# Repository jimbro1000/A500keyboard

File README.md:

# A500 Keyboard HID Adapter
This is a (prototype) project to develop a simple adapter for the Amiga 500 
keyboard for connection via USB. The project is not particularly revolutionary,
other similar projects exist but require the use of more expensive 
microcontrollers while this solution aims to use the remarkably cheap RP2040
controller (aka Raspberry Pico)

## Components Used
Right now this is being built on a breadboard but the design is mirrored as
a KiCad project.

The initial approach is to utilise a pair of CD4050 hex non-inverting buffers
to manage level shifting between the keyboard (which operates at 5v) and the
RP2040 (operating at 3.3v).

The shift up to 5v is only required to drive LEDs on the keyboard so not actually
mandatory but in order to achieve full brightness the 5v is needed. This could
be achieved with a couple of transistors but the CD4050 chips are cheap enough
and readily available such that it is an equally simply solution.

If you don't care about the brightness of the LEDs then you could simply miss
the second CD4050 out and just jumper between two pairs of pins.

The inclusion of smoothing caps on the board is equally speculative. For the LED
drivers it should be completely unnecessary given the frequencies used. For the
keyboard data lines though it is strongly recommended to make sure the quality 
of transmission is maintained.

All in a single prepared board should cost roughly £14 (being somewhat pessimistic
with component prices). Given the price point on the PCB in batches of 10 and
similar bulk prices on the Pico board that could easily be reduced down to just 
£9 (being optimistic). Deleting the second CD4050 should save another £0.20-0.60
(if you're paying more that for CD4050s something is wrong).

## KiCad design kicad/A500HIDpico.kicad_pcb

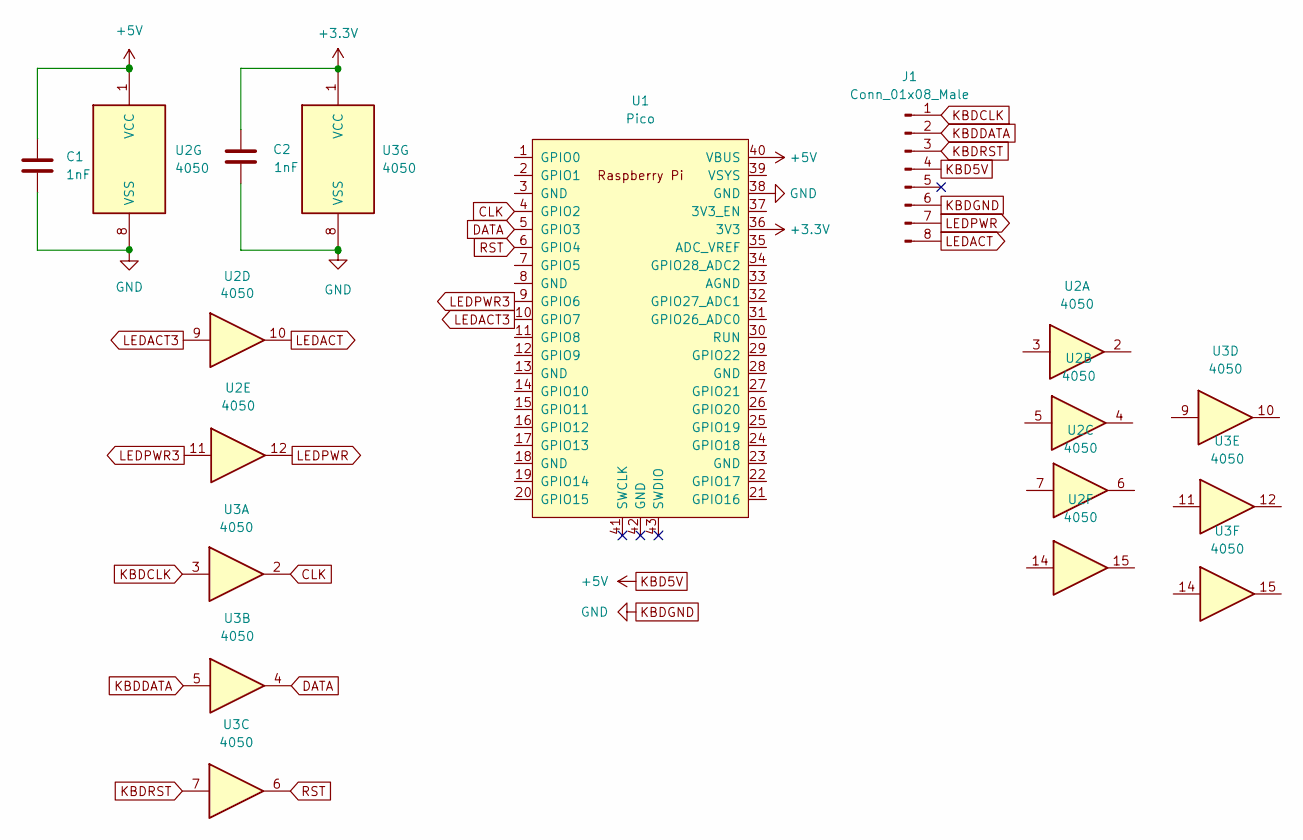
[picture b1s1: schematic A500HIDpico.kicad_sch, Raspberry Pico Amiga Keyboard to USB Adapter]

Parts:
C1, C2: 1nF; C_Disc_D4.3mm_W1.9mm_P5.00mm
J1: Conn_01x08_Male; PinHeader_1x08_P2.54mm_Vertical
U1: Pico; RPi_Pico_SMD_TH
U2, U3: 4050; DIP-16_W7.62mm

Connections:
+3V3: C2.1, U1.36 (3V3), U3.1 (VCC)
CLK: U1.4 (GPIO2), U3.2
DATA: U1.5 (GPIO3), U3.4
KBD5V: C1.1, J1.4, U1.40 (VBUS), U2.1 (VCC)
KBDCLK: J1.1, U3.3
KBDDATA: J1.2, U3.5
KBDGND: C1.2, C2.2, J1.6, U1.38 (GND), U2.8 (VSS), U3.8 (VSS)
KBDRST: J1.3, U3.7
LEDACT: J1.8, U2.10
LEDACT3: U1.10 (GPIO7), U2.9
LEDPWR: J1.7, U2.12
LEDPWR3: U1.9 (GPIO6), U2.11
RST: U1.6 (GPIO4), U3.6

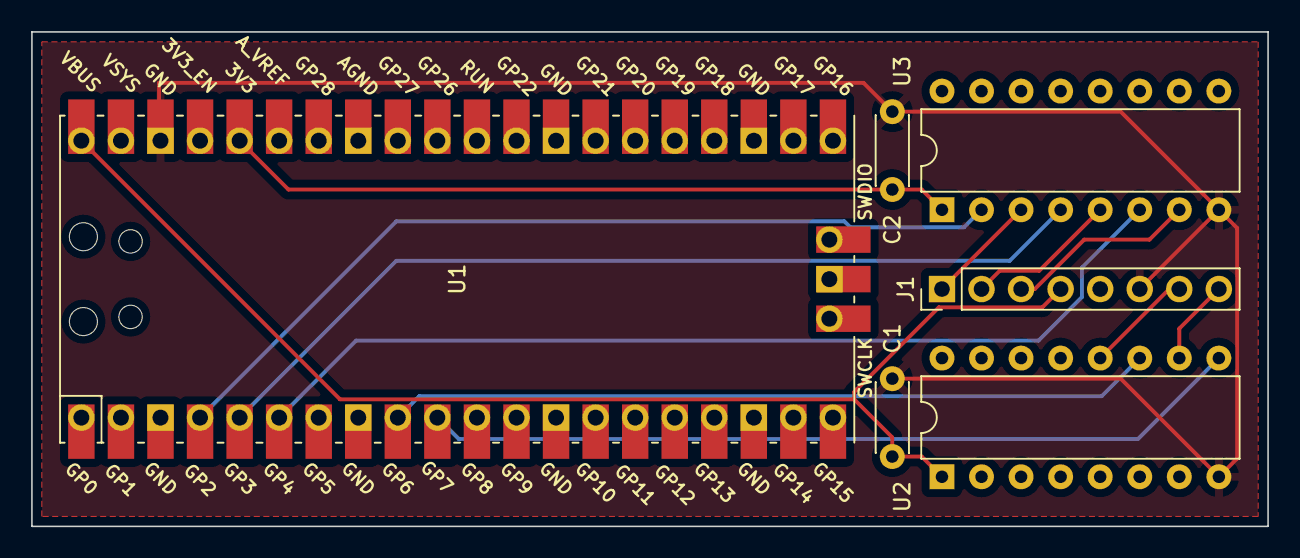
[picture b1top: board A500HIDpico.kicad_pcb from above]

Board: 2 copper layers, 79.4 x 31.8 mm, 6 parts (0 on the bottom side), 13 nets.
